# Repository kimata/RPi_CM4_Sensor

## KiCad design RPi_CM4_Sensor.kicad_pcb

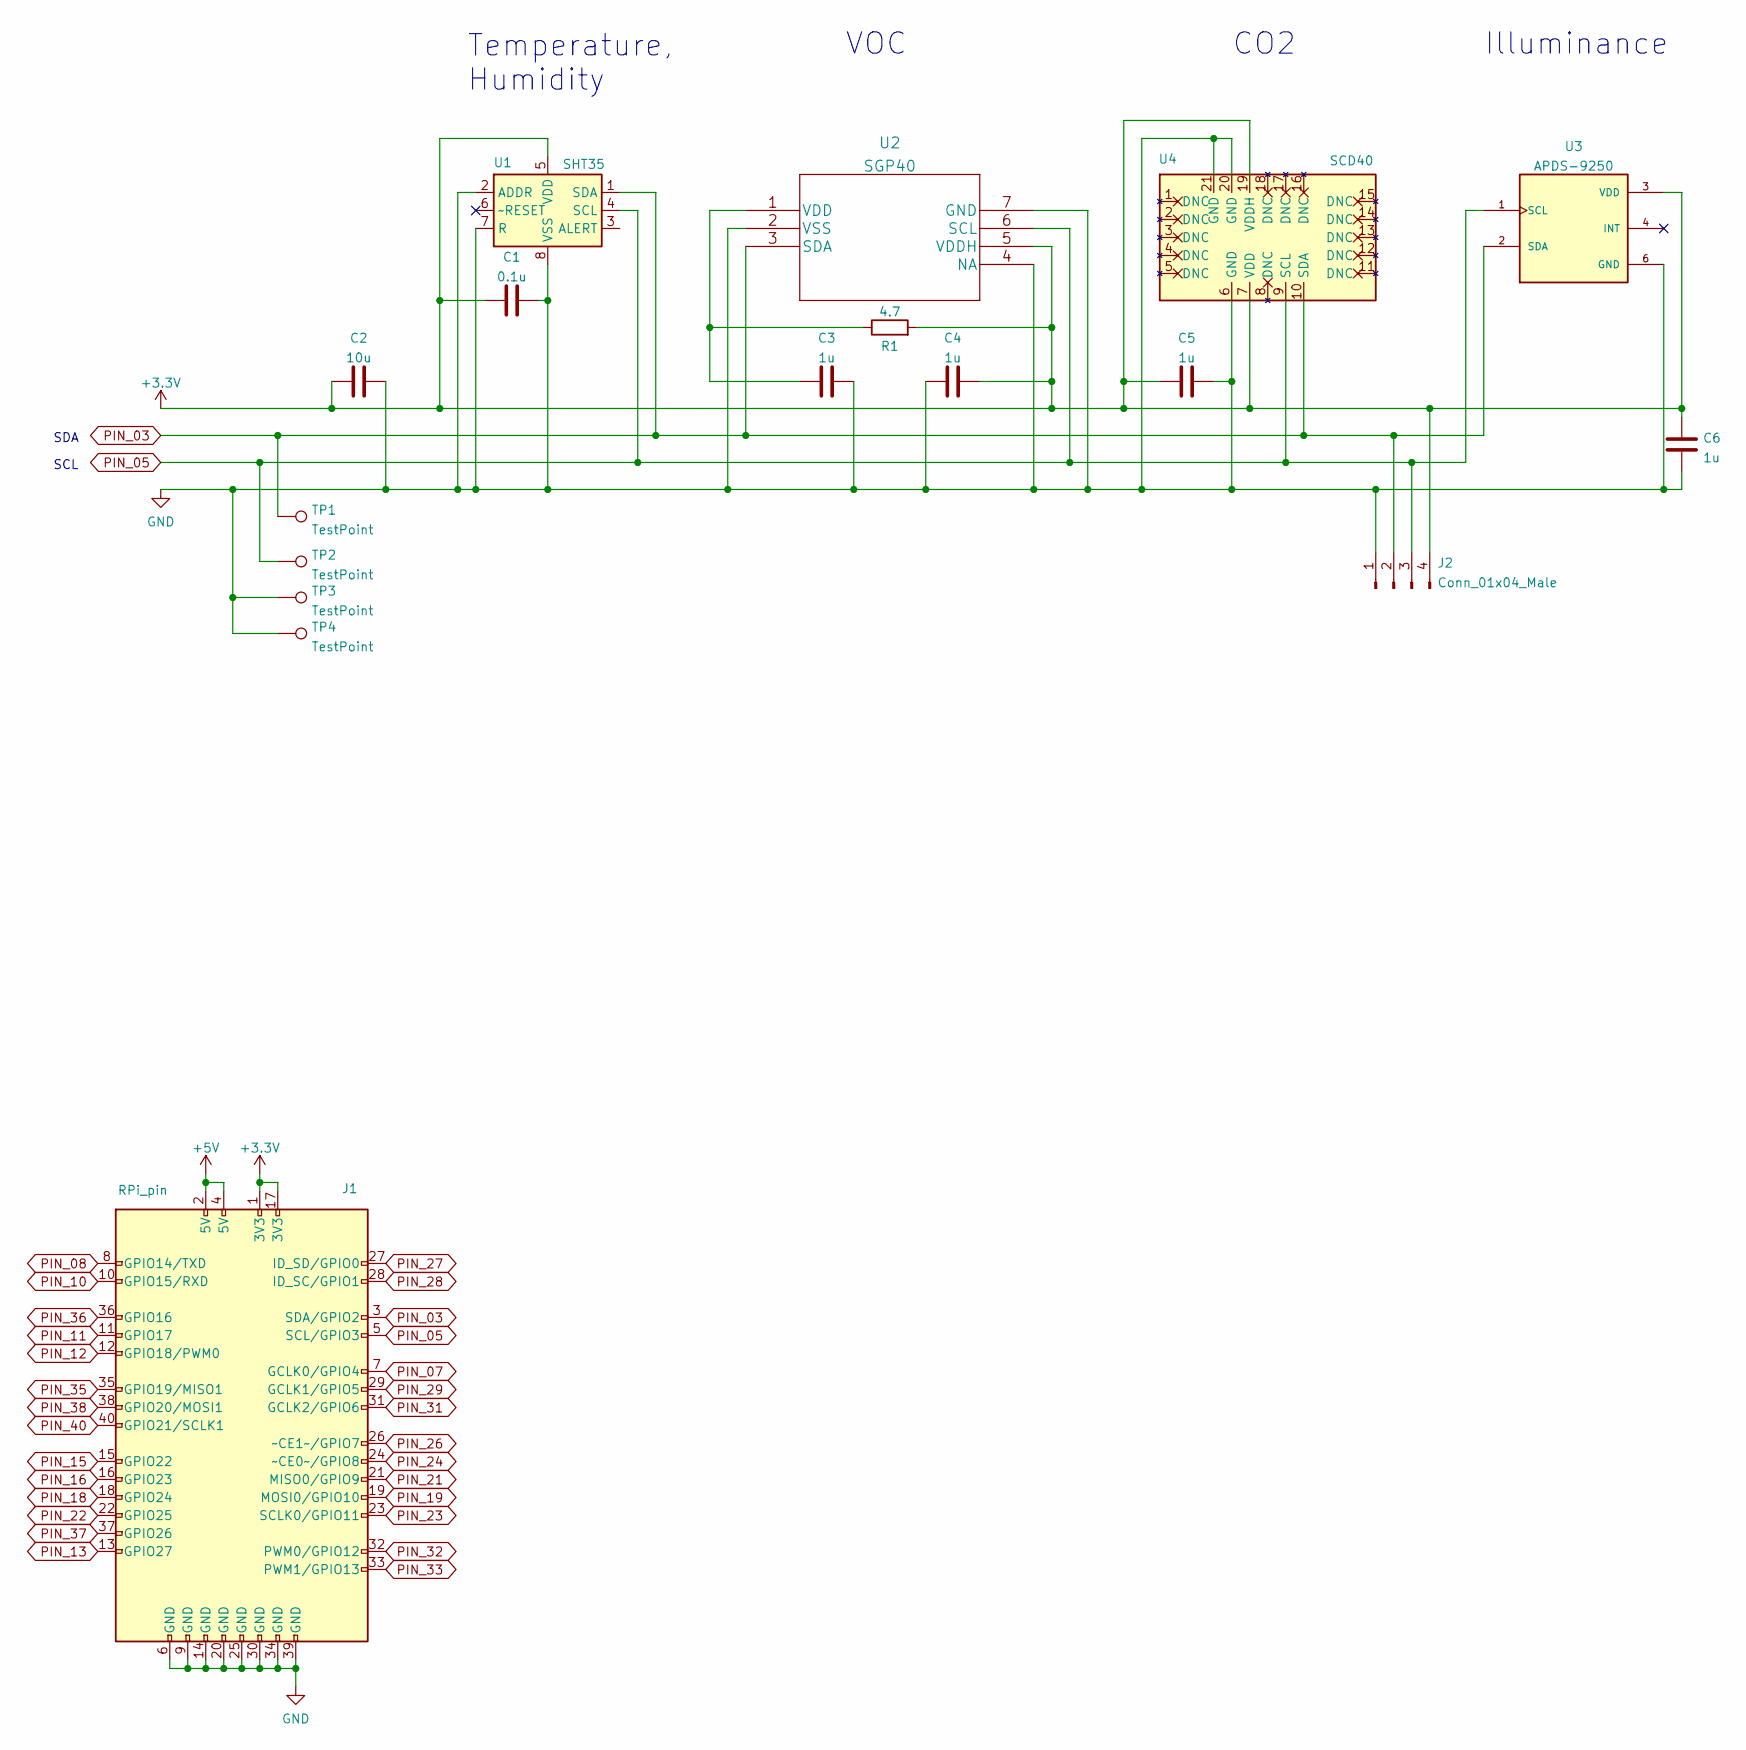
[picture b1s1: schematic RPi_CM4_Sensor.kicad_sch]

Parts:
C1: 0.1u; C_0805_2012Metric_Pad1.18x1.45mm_HandSolder
C2: 10u; C_1206_3216Metric_Pad1.33x1.80mm_HandSolder
C3, C4, C5, C6: 1u; C_0805_2012Metric_Pad1.18x1.45mm_HandSolder
J1: RPi_pin; PinHeader_2x20_P2.54mm_Vertical
J2: Conn_01x04_Male; PinHeader_1x04_P2.54mm_Vertical
R1: 4.7; R_0805_2012Metric_Pad1.20x1.40mm_HandSolder
TP1, TP2, TP3, TP4: TestPoint; TestPoint_Loop_D2.54mm_Drill1.5mm_Beaded
U1: SHT35; Sensirion_DFN-8-1EP_2.5x2.5mm_P0.5mm_EP1.1x1.7mm
U2: SGP40; SGP40-D-R4
U3: APDS-9250; SON65P200X200X75-6N
U4: SCD40; SCD4x

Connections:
+3V3: C1.1, C2.1, C4.2, C5.1, C6.1, J1.1 (3V3), J1.17 (3V3), J2.4, R1.2, U1.5 (VDD), U2.5 (VDDH), U3.3 (VDD), U4.7 (VDD), U4.19 (VDDH)
+5V: J1.2 (5V), J1.4 (5V)
GND: C1.2, C2.2, C3.2, C4.1, C5.2, C6.2, J1.6 (GND), J1.9 (GND), J1.14 (GND), J1.20 (GND), J1.25 (GND), J1.30 (GND), J1.34 (GND), J1.39 (GND), J2.1, TP3.1, TP4.1, U1.2 (ADDR), U1.7 (R), U1.8 (VSS), U1.9 (VSS), U2.2 (VSS), U2.4 (NA), U2.7 (GND), U3.6 (GND), U4.6 (GND), U4.20 (GND), U4.21 (GND)
unnamed: C3.1, R1.1, U2.1 (VDD)
PIN_03: J1.3 (SDA/GPIO2), J2.2, TP1.1, U1.1 (SDA), U2.3 (SDA), U3.2 (SDA), U4.10 (SDA)
PIN_05: J1.5 (SCL/GPIO3), J2.3, TP2.1, U1.4 (SCL), U2.6 (SCL), U3.1 (SCL), U4.9 (SCL)
PIN_07: J1.7 (GCLK0/GPIO4)
PIN_08: J1.8 (GPIO14/TXD)
PIN_10: J1.10 (GPIO15/RXD)
PIN_11: J1.11 (GPIO17)
PIN_12: J1.12 (GPIO18/PWM0)
PIN_13: J1.13 (GPIO27)
PIN_15: J1.15 (GPIO22)
PIN_16: J1.16 (GPIO23)
PIN_18: J1.18 (GPIO24)
PIN_19: J1.19 (MOSI0/GPIO10)
PIN_21: J1.21 (MISO0/GPIO9)
PIN_22: J1.22 (GPIO25)
PIN_23: J1.23 (SCLK0/GPIO11)
PIN_24: J1.24 (~CE0~/GPIO8)
PIN_26: J1.26 (~CE1~/GPIO7)
PIN_27: J1.27 (ID_SD/GPIO0)
PIN_28: J1.28 (ID_SC/GPIO1)
PIN_29: J1.29 (GCLK1/GPIO5)
PIN_31: J1.31 (GCLK2/GPIO6)
PIN_32: J1.32 (PWM0/GPIO12)
PIN_33: J1.33 (PWM1/GPIO13)
PIN_35: J1.35 (GPIO19/MISO1)
PIN_36: J1.36 (GPIO16)
PIN_37: J1.37 (GPIO26)
PIN_38: J1.38 (GPIO20/MOSI1)
PIN_40: J1.40 (GPIO21/SCLK1)

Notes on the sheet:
SDA
SCL
Temperature, Humidity
VOC
CO2
Illuminance

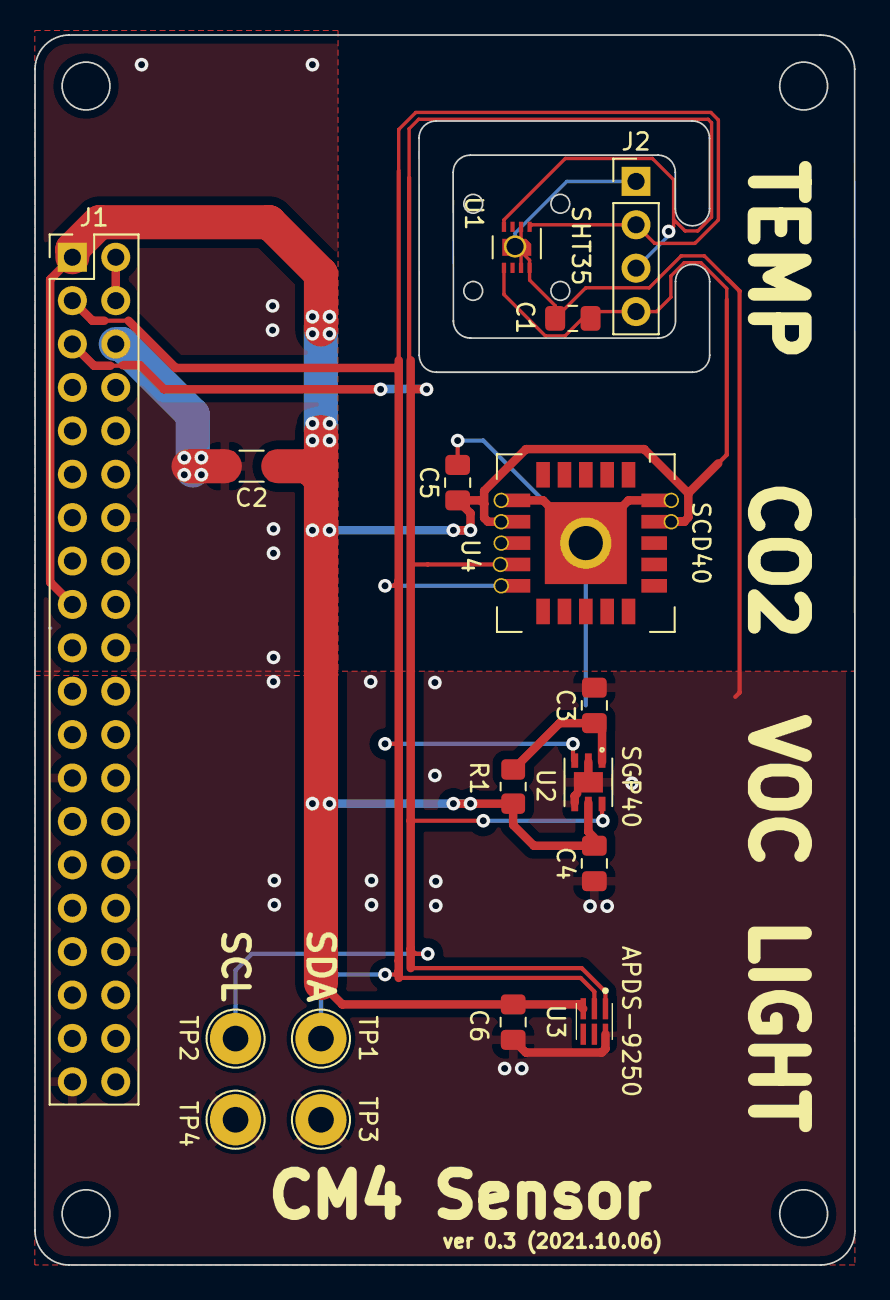
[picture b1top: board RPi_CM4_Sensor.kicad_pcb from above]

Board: 2 copper layers, 48.0 x 72.0 mm, 17 parts (0 on the bottom side), 6 nets.

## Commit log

2021-08-21 feat: とりあえず完成
2021-08-27 fix: SCD4x の穴径を修正
2021-10-05 fix: 微修正
2021-10-06 feat: 温度センサを別基板に配置するためのピンヘッダを追加
2023-12-15 Add renovate.json
